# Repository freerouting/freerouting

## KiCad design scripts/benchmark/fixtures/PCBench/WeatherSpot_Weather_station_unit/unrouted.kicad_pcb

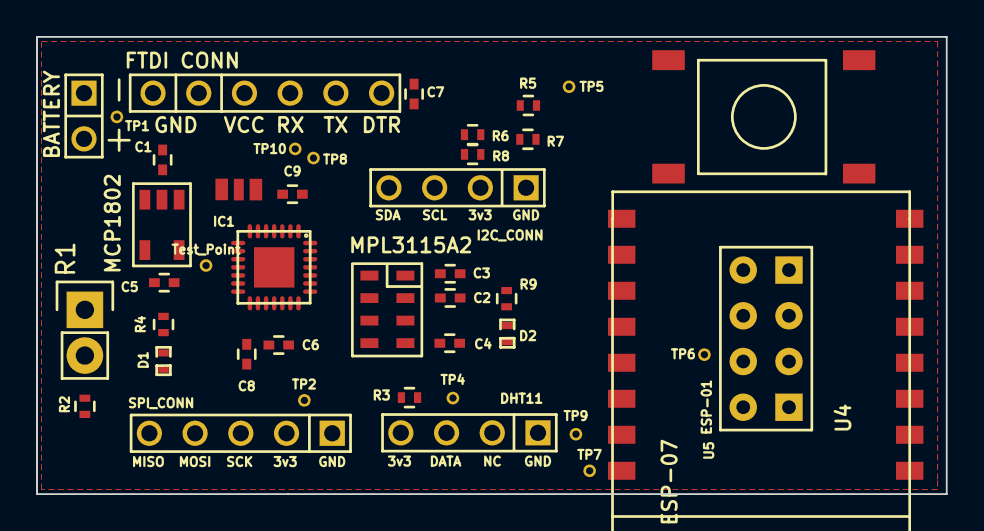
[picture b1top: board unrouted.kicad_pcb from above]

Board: 2 copper layers, 50.5 x 25.4 mm, 42 parts (0 on the bottom side), 24 nets, no tracks yet.

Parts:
BT1: BATTERY; BATT_CONN
C1, C5: 1uF; C_0402
C2, C4: 100nF; C_0402
C3: 10uF; C_0402
C6, C7, C8, C9: 0.1uF; C_0402
D1, D2: LED; SMD-0402_LED
IC1: ATMEGA328P-MM; QFN-28-4x4mm_fixed_mask
P1: FTDI CONN; FTDI_PORT
Q1: Oscilator; ceramic_resonator_smd
R1: PhotoResistor; Socket_Strip_Straight_1x02
R2, R5, R7: 10K; R_0402
R3: 5K; R_0402
R4, R9: 470; R_0402
R6, R8: 4.7K; R_0402
SW1: SW_PUSH; push_switch_SMD
TP1: TP1; TEST_POINT
TP2: TP2; TEST_POINT
TP3: Test_Point; TEST_POINT
TP4: TP4; TEST_POINT
TP5: TP5; TEST_POINT
TP6: TP6; TEST_POINT
TP7: TP7; TEST_POINT
TP8: TP8; TEST_POINT
TP9: TP9; TEST_POINT
TP10: TP10; TEST_POINT
U1: MPL3115A2
U2: MCP1802; MCP1802T
U3: DHT11
U4: ESP-07
U5: ESP-01
conn1: I2C_CONN
conn2: SPI_CONN

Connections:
3V3: C3.1, C4.1, C5.1, C8.1, C9.1, D2.2, IC1.3, IC1.16, R1.1, R3.1, R5.1, R6.1, R7.1, R8.1, TP2.1, TP3.1, U1.1, U1.4, U2.5, U3.1, U4.8, U5.4, conn1.3, conn2.4
/D2: IC1.28, R3.2, TP4.1, U3.2
/DTR: C7.1, P1.6
/MISO: IC1.14, conn2.1
/MOSI: IC1.13, conn2.2
/RX: IC1.26, P1.4, TP10.1
/RXS: IC1.1, TP9.1, U4.15, U5.5
/SCK: IC1.15, R4.2, conn2.3
/TX: IC1.27, P1.5, TP8.1
/TXS: IC1.2, TP7.1, U4.16, U5.1
/VCC: BT1.1, C1.1, P1.3, TP1.1, U2.1, U2.3
A0: IC1.19, R1.2, R2.1
GND: BT1.2, C1.2, C2.2, C3.2, C4.2, C5.2, C6.2, C8.2, C9.2, D1.2, IC1.4, IC1.18, P1.1, P1.2, Q1.1, R2.2, R9.2, SW1.2, U1.3, U2.2, U3.4, U4.9, U5.8, conn1.4, conn2.5
unnamed: C2.1, U1.2
unnamed: C6.1, IC1.17
unnamed: C7.2, IC1.25, R5.2, SW1.1, TP5.1
unnamed: D1.1, R4.1
unnamed: D2.1, R9.1
unnamed: IC1.5, Q1.3
unnamed: IC1.6, Q1.2
unnamed: R7.2, U4.3, U5.2
unnamed: TP6.1, U5.3
SCL: IC1.24, R8.2, U1.8, conn1.2
SDA: IC1.23, R6.2, U1.7, conn1.1

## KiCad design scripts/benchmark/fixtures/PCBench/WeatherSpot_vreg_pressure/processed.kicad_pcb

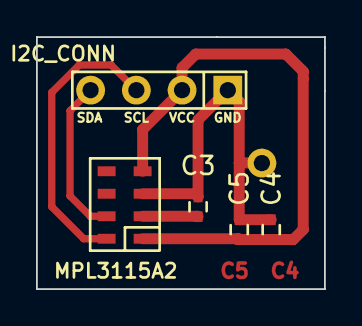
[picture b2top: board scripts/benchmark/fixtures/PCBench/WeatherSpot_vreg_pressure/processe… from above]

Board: 2 copper layers, 16.0 x 14.0 mm, 6 parts (0 on the bottom side), 5 nets.

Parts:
C3, C5: 0.1uF; C_0402
C4: 10uF; C_0402
U1: MPL3115A2
VIA_HOME_ETCH: VAL**; VIA_HOME_ETCH
conn1: I2C_CONN

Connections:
3V3: C4.1, C5.1, U1.1, U1.4, conn1.3
GND: C3.2, C4.2, C5.2, U1.3, VIA_HOME_ETCH.1, conn1.4
unnamed: C3.1, U1.2
unnamed: U1.7, conn1.1
unnamed: U1.8, conn1.2

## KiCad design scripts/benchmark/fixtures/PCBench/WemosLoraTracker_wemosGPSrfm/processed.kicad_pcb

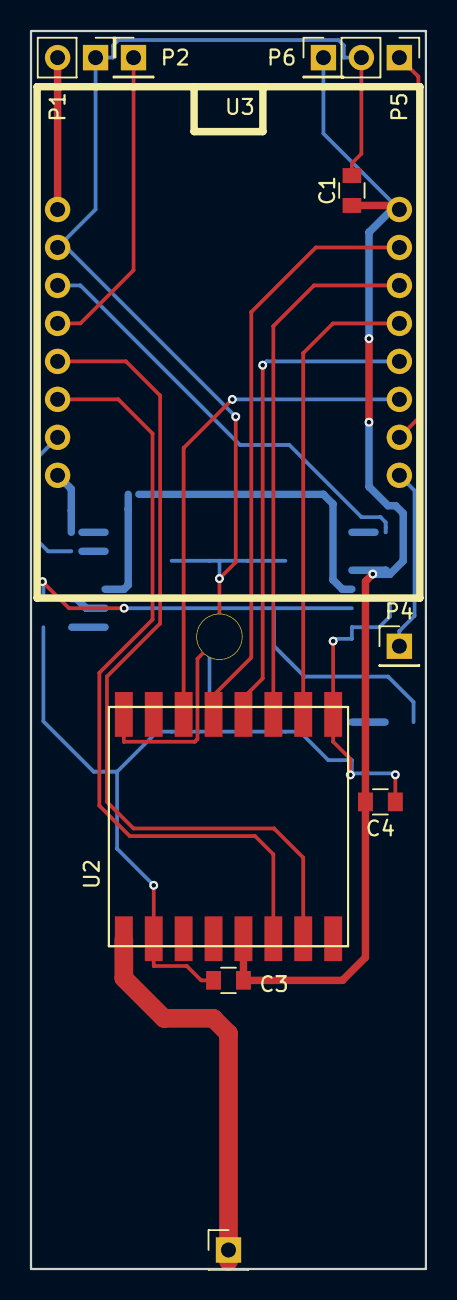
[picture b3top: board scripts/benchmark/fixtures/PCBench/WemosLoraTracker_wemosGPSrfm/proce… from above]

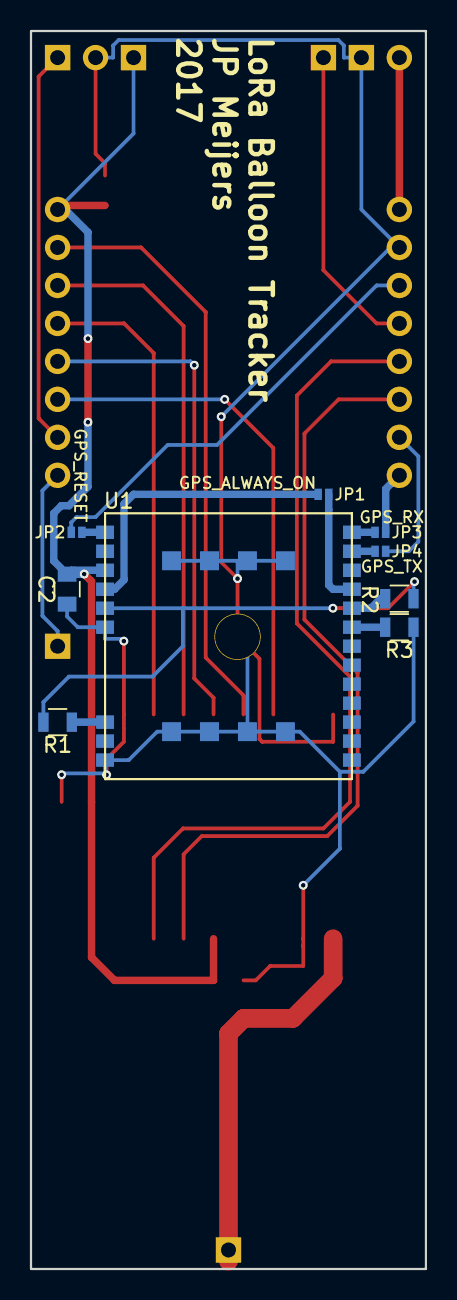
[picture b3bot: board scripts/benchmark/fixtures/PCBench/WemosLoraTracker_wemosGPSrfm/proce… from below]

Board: 2 copper layers, 26.4 x 82.8 mm, 20 parts (9 on the bottom side), 26 nets.

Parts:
C1, C4: 10uF; C_0805
C2, C3: 100nF; C_0805
JP1: GPS_ALWAYS_ON; S_JUMPER_2
JP2: GPS_RESET; S_JUMPER_2
JP3: GPS_RX; S_JUMPER_2
JP4: GPS_TX; S_JUMPER_2
P1: BATTERY; Socket_Strip_Straight_1x02_Pitch2.54mm
P2: CONN_DIO0; Socket_Strip_Straight_1x01_Pitch2.54mm
P3, P6: CONN_01X01; Socket_Strip_Straight_1x01_Pitch2.54mm
P4: RESET; Socket_Strip_Straight_1x01_Pitch2.54mm
P5: ADC_INPUT; Socket_Strip_Straight_1x02_Pitch2.54mm
R1: 10k; R_0805
R2, R3: 2k2; R_0805
U1: GPS_A2235-H
U2: RFM95
U3: WEMOS_D1_mini

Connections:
/3V3: C1.1, C2.1, C3.1, C4.1, P6.1, U1.3, U2.13, U3.16
/5V: P1.2, U3.1
/ADC: P5.1, U3.10
/DIO0: P2.1, U3.4
/DIO1/TX: JP3.2, U3.8
/DIO2: JP2.2, U3.3
/DIO3/RX: JP4.2, U3.7
/DIO4/rfmDIO1: U2.15, U3.5
/DIO5/rfmDIO0: U2.14, U3.6
/DIO12/MISO: U2.2, U3.13
/DIO13/MOSI: U2.3, U3.14
/DIO14/SCK: U2.4, U3.12
/DIO15/SS: U2.5, U3.15
/DIO16/rfmRESET: U2.6, U3.11
/GND: C1.2, C2.2, C3.2, C4.2, P1.1, P5.2, R3.2, U1.6, U1.9, U1.23, U1.24, U1.25, U1.26, U1.27, U1.28, U1.29, U1.30, U1.31, U2.1, U2.8, U2.10, U3.2
/GPS_1V8: R1.1, R2.2, U1.5
/GPS_RESET: JP2.1, U1.1
/GPS_RX: JP3.1, U1.22
/GPS_TX: JP4.1, U1.21
/RST: P4.1, U3.9
unnamed: JP1.1, U1.4
unnamed: JP1.2, U1.19
unnamed: P3.1, U2.9
unnamed: R1.2, U1.7
unnamed: R2.1, U1.18
unnamed: R3.1, U1.17

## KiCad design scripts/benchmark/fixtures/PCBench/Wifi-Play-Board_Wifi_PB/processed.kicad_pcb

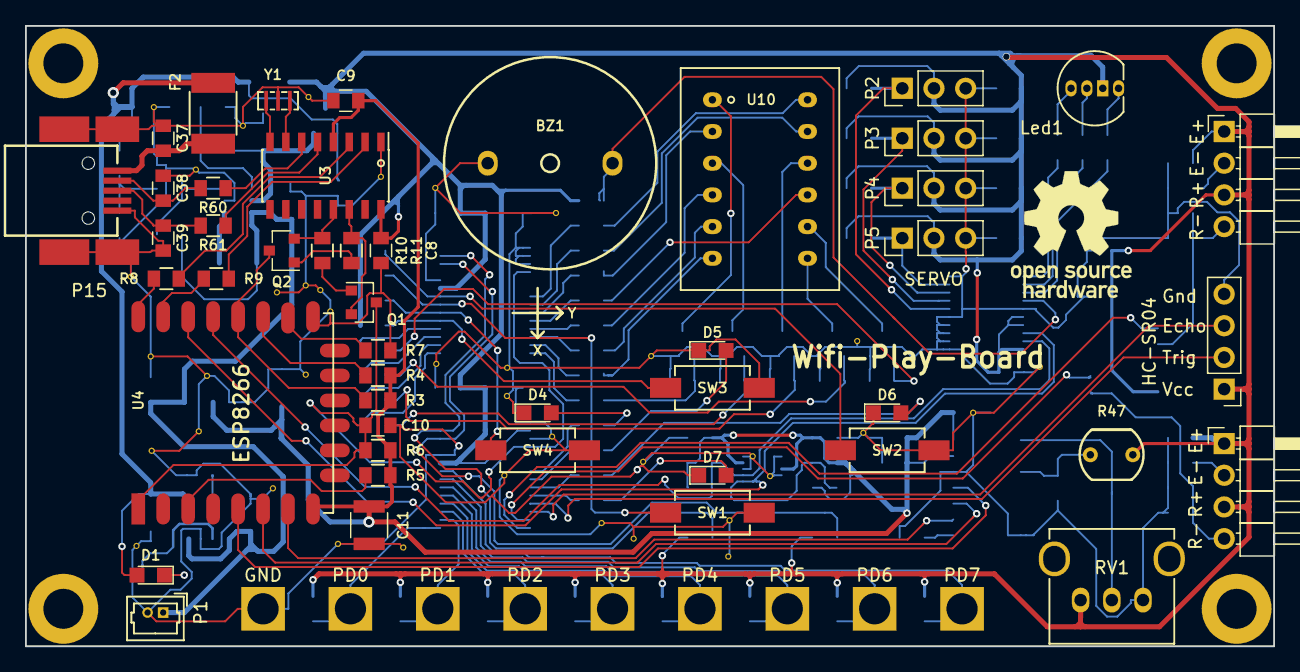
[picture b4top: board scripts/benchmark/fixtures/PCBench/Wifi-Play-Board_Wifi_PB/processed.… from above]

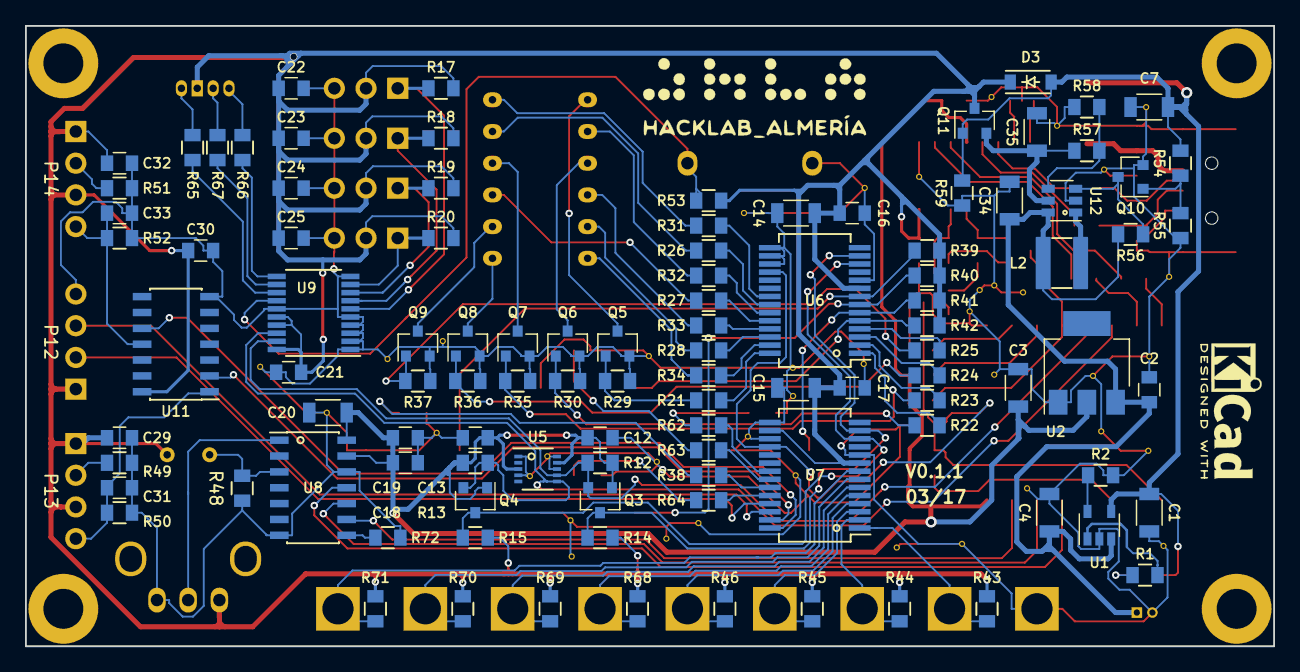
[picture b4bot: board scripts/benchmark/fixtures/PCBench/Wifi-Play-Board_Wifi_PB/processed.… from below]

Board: 2 copper layers, 100.0 x 49.7 mm, 200 parts (105 on the bottom side), 111 nets.

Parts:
BZ1: Buzzer; LOUDITY_LD-BZPN-1705
C1, C4, C14, C15, C20, C34: 4u7; C_1206
C2, C8, C9, C12, C13, C16, C17, C18, C19, C21, C29, C30, C32: 100n; C_0805
C3, C7, C35: 10u; C_1206
C10: 0.47n; C_0805
C11: 100u; C_1210
C22, C23, C24, C25: 1u; C_0805
C31, C33, C37: 10n; C_0805
C38, C39: 0,047n; C_0805
D1, D4, D5, D6, D7: LED; LED_0805
D3: MBR0520; SOD-123
F2: F; R_1812
Gnd-Via: VAL**; Gnd-Via
Gnd-Via_2, Gnd-Via_3, Gnd-Via_4, Gnd-Via_5, Gnd-Via_6, Gnd-Via_7, Gnd-Via_8, Gnd-Via_9, Gnd-Via_10, Gnd-Via_11, Gnd-Via_12, Gnd-Via_13, Gnd-Via_14, Gnd-Via_15, Gnd-Via_16, Gnd-Via_17, Gnd-Via_18, Gnd-Via_19, Gnd-Via_20, Gnd-Via_21, Gnd-Via_22, Gnd-Via_23, Gnd-Via_24, Gnd-Via_25, Gnd-Via_26, Gnd-Via_27, Gnd-Via_28, Gnd-Via_29, Gnd-Via_30, Gnd-Via_31, Gnd-Via_32, Gnd-Via_33, Gnd-Via_34, Gnd-Via_35, Gnd-Via_36, Gnd-Via_37, Gnd-Via_38, Gnd-Via_39: VAL**; Gnd-Via
L2: 4u7; BOURNS_SRN4012T
Led1: Led_RGB; LED_RGB_5mm_G_B_COM_R_Anodo_comun
P1: CONN_01X02; Molex_PicoBlade_53047-0210_02x1.25mm_Straight
P2, P3, P4, P5: CONN_01X03; Pin_Header_Straight_1x03_Pitch2.54mm
P6, P7, P8, P9, P10, P16, P17, P18, P19: CONN_01X01; Pad_Conector_Cocodrilo
P12: CONN_01X04; Socket_Strip_Straight_1x04_Pitch2.54mm
P13, P14: CONN_01X04; Pin_Header_Angled_1x04_Pitch2.54mm
P15: USB_MINI; usb_mini_molex_675031020
Q1, Q2, Q5, Q6, Q7, Q8, Q9: SMBT3904; SOT-23
Q3, Q4: BSS138; SOT-23
Q10: BC849; SOT-23
Q11: NX2301P; SOT-23
R1, R2, R8, R9: 470; R_0805
R3, R4, R5, R6, R7, R10, R11, R17, R18, R19, R20, R39, R40, R41, R42, R53, R56, R59: 10K; R_0805
R12, R13, R14, R15: 4K7; R_0805
R21, R22, R23, R24, R25, R48, R54: 1K; R_0805
R26, R27, R28, R31, R32, R33, R34, R65, R66, R67: 120; R_0805
R29, R30, R35, R36, R37, R50, R52, R55, R72: 47K; R_0805
R38, R62, R63, R64: 220; R_0805
R43, R44, R45, R46, R68, R69, R70, R71: 10M; R_0805
R47: LDR; LDR_TOKEN_PGM5_Series
R49, R51: 220R; R_0805
R57: 976K; R_0805
R58: 309K; R_0805
R60, R61: 22R; R_0805
RV1: POT; ALP_RK09K111
SW1, SW2, SW3, SW4: Pulsador_2p; CANAL_ELECTRONIC_DTSM-31N-B
U1: MCP73831T; SOT-23-5
U2: LD1117S33TR; SOT-223
U3: CH340G; SOIC-16_3.9x9.9mm_Pitch1.27mm
U4: ESP8266; ESP-12E
U5: MMA7660FC; DFN-10-1EP_3x3mm_Pitch0.5mm
U6, U7: MCP23017; SSOP-28_5.3x10.2mm_Pitch0.65mm
U8: MCP3204; SOIC-14_3.9x8.7mm_Pitch1.27mm
U9: PCA9634; TSSOP-20_4.4x6.5mm_Pitch0.65mm
U10: Matriz_5x7_Anodo_Filas; Matriz_Led_7X5
U11: 40106; SOIC-14_3.9x8.7mm_Pitch1.27mm
U12: MCP1640; SOT-23-6
Y1: Cristal; Murata_CSTCE_V_A

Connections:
+3V3: C3.1, C9.1, C11.1, C12.1, C13.1, C18.1, C19.1, C20.1, Q3.1, Q4.1, R3.2, R4.2, R5.2, R6.2, R12.1, R13.1, U2.2, U3.4, U4.8, U5.3, U5.9, U8.13, U8.14
+5V: C8.1, C14.1, C15.1, C16.1, C17.1, C21.1, C22.1, C23.1, C24.1, C25.1, C29.1, C30.1, C32.1, D3.1, Led1.3, P2.2, P3.2, P4.2, P5.2, P12.1, P13.1, P13.3, P14.1, P14.3, Q11.3, R14.1, R15.1, R17.1, R18.1, R19.1, R20.1, R39.1, R40.1, R41.1, R42.1, R43.1, R44.1, R45.1, R46.1, R47.1, R53.1, R68.1, R69.1, R70.1, R71.1, RV1.1, U3.16, U6.9, U7.9, U7.16, U9.16, U9.17, U9.20, U11.14
/Control/EN: R5.1, U4.3
/Control/GPIO0: Q2.3, R3.1, U4.18
/Control/GPIO2: R4.1, U4.17
/Control/GPIO15: R7.1, U4.16
/Control/RxD: R9.1, U4.21
/Control/TxD: R8.1, U4.22
/Control/USBD+: R61.1, U3.5
/Control/USBD-: R60.1, U3.6
BUZZER: BZ1.1, R53.2, U9.14
CH0: RV1.2, U8.1
CH2: R47.2, R48.2, U8.3
GND: BZ1.2, C1.2, C2.2, C3.2, C4.2, C7.2, C8.2, C9.2, C10.2, C11.2, C12.2, C13.2, C14.2, C15.2, C16.2, C17.2, C18.2, C19.2, C20.2, C21.2, C22.2, C23.2, C24.2, C25.2, C29.2, C30.2, C31.2, C32.2, C33.2, C34.2, C35.2, C37.2, C38.2, C39.2, D4.1, D5.1, D6.1, D7.1, Gnd-Via.1, Gnd-Via_2.1, Gnd-Via_3.1, Gnd-Via_4.1, Gnd-Via_5.1, Gnd-Via_6.1, Gnd-Via_7.1, Gnd-Via_8.1, Gnd-Via_9.1, Gnd-Via_10.1, Gnd-Via_11.1, Gnd-Via_12.1, Gnd-Via_13.1, Gnd-Via_14.1, Gnd-Via_15.1, Gnd-Via_16.1, Gnd-Via_17.1, Gnd-Via_18.1, Gnd-Via_19.1, Gnd-Via_20.1, Gnd-Via_21.1, Gnd-Via_22.1, Gnd-Via_23.1, Gnd-Via_24.1, Gnd-Via_25.1, Gnd-Via_26.1, Gnd-Via_27.1, Gnd-Via_28.1, Gnd-Via_29.1, Gnd-Via_30.1, Gnd-Via_31.1, Gnd-Via_32.1, Gnd-Via_33.1, Gnd-Via_34.1, Gnd-Via_35.1, Gnd-Via_36.1, Gnd-Via_37.1, Gnd-Via_38.1, Gnd-Via_39.1, P1.2, P2.3, P3.3, P4.3, P5.3, P10.1, P12.4, P15.5, P15.6, Q5.2, Q6.2, Q7.2, Q8.2, Q9.2, Q10.2, R2.2, R7.2, R29.2, R30.2, R35.2, R36.2, R37.2, R48.1, R49.2, R50.2, R51.2, R52.2, R55.2, R58.2, R59.1, R72.2, RV1.3, SW1.1, SW2.1, SW3.1, SW4.1, U1.2, U2.1, U3.1, U4.15, U5.1, U5.4, U5.8, U5.10, U6.10, U6.15, U6.16, U6.17, U7.10, U7.15, U7.17, U8.7, U8.12, U9.1, U9.2, U9.3, U9.4, U9.5, U9.10, U9.15, U11.7, U12.2, Y1.2
LED_BLUE: R67.2, U9.12
LED_GREEN: R66.2, U9.11
LED_RED: R65.2, U9.13
MISO: U4.6, U8.10
MOSI: U4.7, U8.9
unnamed: C31.1, P13.4, R50.1, U11.1
unnamed: C33.1, P14.4, R52.1, U11.11
unnamed: C37.1, F2.2, P15.1
unnamed: C38.1, P15.2, R60.2
unnamed: C39.1, P15.3, R61.2
unnamed: D1.1, R1.2
unnamed: D4.2, R62.2
unnamed: D5.2, R63.2
unnamed: D6.2, R38.2
unnamed: D7.2, R64.2
unnamed: L2.2, U12.1
unnamed: Led1.1, R66.1
unnamed: Led1.2, R67.1
unnamed: Led1.4, R65.1
unnamed: P13.2, R49.1
unnamed: P14.2, R51.1
unnamed: Q1.1, R10.1
unnamed: Q1.2, R11.2, U3.14
unnamed: Q2.1, R11.1
unnamed: Q2.2, R10.2, U3.13
unnamed: Q5.1, R21.1, R29.1
unnamed: Q5.3, U10.1
unnamed: Q6.1, R22.1, R30.1
unnamed: Q6.3, U10.3
unnamed: Q7.1, R23.1, R35.1
unnamed: Q7.3, U10.10
unnamed: Q8.1, R24.1, R36.1
unnamed: Q8.3, U10.7
unnamed: Q9.1, R25.1, R37.1
unnamed: Q9.3, U10.8
unnamed: Q10.1, R54.1, R55.1
unnamed: Q10.3, R56.1, U12.3
unnamed: R1.1, U1.1
unnamed: R2.1, U1.5
unnamed: R8.2, U3.3
unnamed: R9.2, U3.2
unnamed: R26.1, U10.11
unnamed: R27.1, U10.9
unnamed: R28.1, U10.5
unnamed: R31.1, U10.12
unnamed: R32.1, U10.2
unnamed: R33.1, U10.4
unnamed: R34.1, U10.6
unnamed: R57.2, R58.1, U12.4
unnamed: R72.1, U8.8
unnamed: U3.7, Y1.1
unnamed: U3.8, Y1.3
PA0: R31.2, U6.21
PA1: R26.2, U6.22
PA2: R32.2, U6.23
PA3: R27.2, U6.24
PA4: R33.2, U6.25
PA5: R28.2, U6.26
PA6: R34.2, U6.27
PA7: R21.2, U6.28
PB0: R22.2, U6.1
PB1: R23.2, U6.2
PB2: R24.2, U6.3
PB3: R25.2, U6.4
PB4: R42.2, SW3.2, U6.5
PB5: R41.2, SW4.2, U6.6
PB6: R40.2, SW1.2, U6.7
PB7: R39.2, SW2.2, U6.8
PC0: R62.1, U7.21
PC1: R63.1, U7.22
PC2: R38.1, U7.23
PC3: R64.1, U7.24
PC4: P12.2, U7.25
PC5: P12.3, U7.26
PC6: U7.27, U11.2
PC7: U7.28, U11.10
PD0: P6.1, R43.2, U7.1
PD1: P7.1, R44.2, U7.2
PD2: P8.1, R45.2, U7.3
PD3: P9.1, R46.2, U7.4
PD4: P16.1, R68.2, U7.5
PD5: P17.1, R69.2, U7.6
PD6: P18.1, R70.2, U7.7
PD7: P19.1, R71.2, U7.8
SCK: U4.5, U8.11
SCL: Q4.2, R13.2, U4.20, U5.6, U9.18
SCL2: Q4.3, R15.2, U6.12, U7.12
SDA: Q3.2, R12.2, U4.19, U5.7, U9.19
SDA2: Q3.3, R14.2, U6.13, U7.13
SERVO1: P2.1, R17.2, U9.6
SERVO2: P3.1, R18.2, U9.7
SERVO3: P4.1, R19.2, U9.8
SERVO4: P5.1, R20.2, U9.9
V5VBOOST: C35.1, Q11.2, R57.1, U12.5
VBATT: C2.1, C4.1, C34.1, L2.1, P1.1, R56.2, U1.3, U2.3, U12.6
VUSB: C1.1, C7.1, D1.2, D3.2, F2.1, Q11.1, R54.2, R59.2, U1.4
~RESET: C10.1, Q1.3, R6.1, U4.1, U6.18, U7.18
